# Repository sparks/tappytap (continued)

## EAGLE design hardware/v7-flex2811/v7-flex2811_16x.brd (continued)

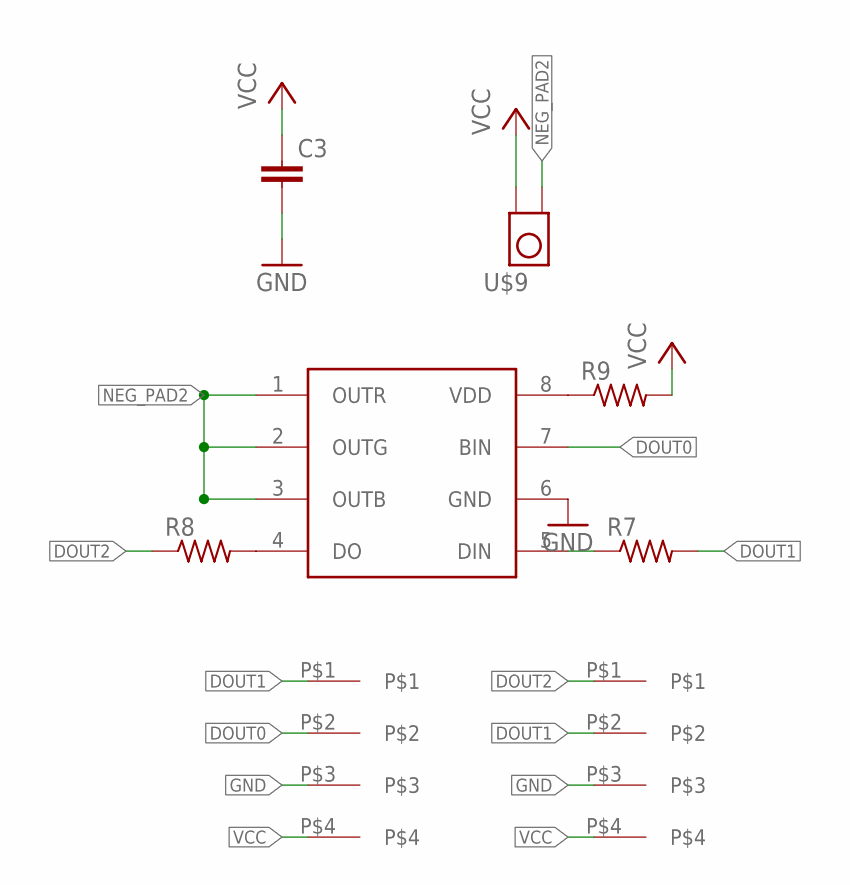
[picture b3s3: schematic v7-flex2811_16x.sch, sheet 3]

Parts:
C3: C-EUC0201; C0201
R7, R8, R9: R-US_R0201; R0201
U$9: TP_4MM_MED_PAD
U$10: WS2818; SO08
U$11, U$12: 4PAD

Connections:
DOUT0: U$10.7 (BIN), U$11.P$2; also elsewhere on the board
DOUT1: R7.2, U$11.P$1, U$12.P$2; also elsewhere on the board
DOUT2: R8.1, U$12.P$1; also elsewhere on the board
GND: C3.2, U$10.6 (GND), U$11.P$3, U$12.P$3; also elsewhere on the board
unnamed: R7.1, U$10.5 (DIN)
unnamed: R8.2, U$10.4 (DO)
unnamed: R9.1, U$10.8 (VDD)
NEG_PAD2: U$9.P$1 (0), U$10.1 (OUTR), U$10.2 (OUTG), U$10.3 (OUTB)
VCC: C3.1, R9.2, U$9.P$2 (1), U$11.P$4, U$12.P$4; also elsewhere on the board

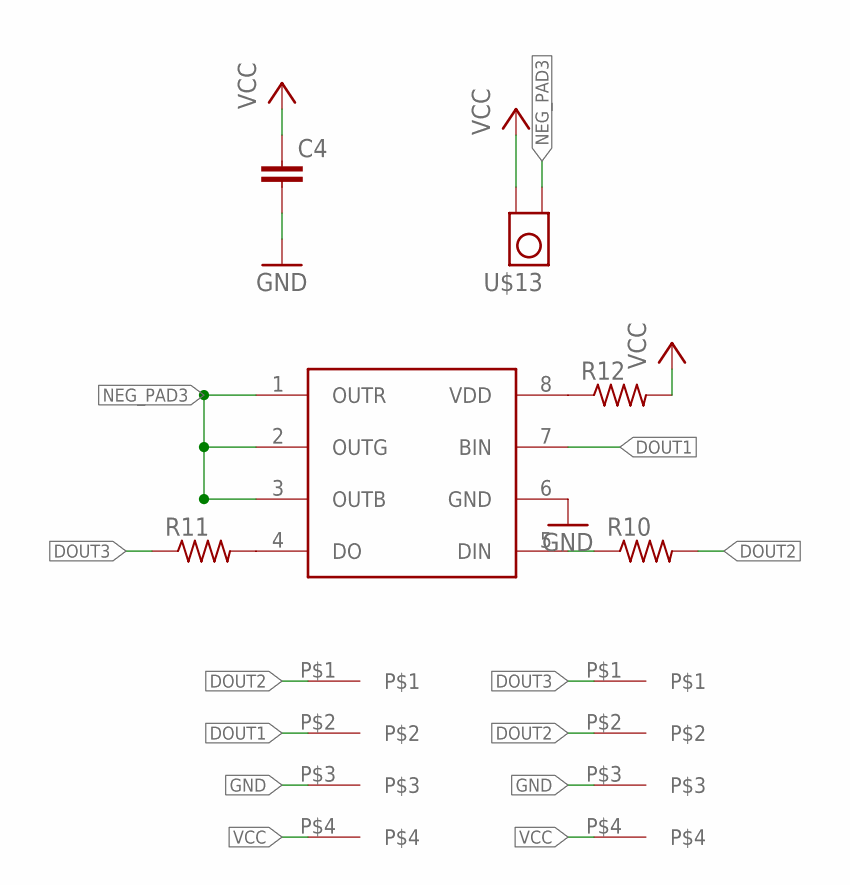
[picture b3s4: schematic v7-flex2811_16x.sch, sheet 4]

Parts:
C4: C-EUC0201; C0201
R10, R11, R12: R-US_R0201; R0201
U$13: TP_4MM_MED_PAD
U$14: WS2818; SO08
U$15, U$16: 4PAD

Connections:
DOUT1: U$14.7 (BIN), U$15.P$2; also elsewhere on the board
DOUT2: R10.2, U$15.P$1, U$16.P$2; also elsewhere on the board
DOUT3: R11.1, U$16.P$1; also elsewhere on the board
GND: C4.2, U$14.6 (GND), U$15.P$3, U$16.P$3; also elsewhere on the board
unnamed: R10.1, U$14.5 (DIN)
unnamed: R11.2, U$14.4 (DO)
unnamed: R12.1, U$14.8 (VDD)
NEG_PAD3: U$13.P$1 (0), U$14.1 (OUTR), U$14.2 (OUTG), U$14.3 (OUTB)
VCC: C4.1, R12.2, U$13.P$2 (1), U$15.P$4, U$16.P$4; also elsewhere on the board

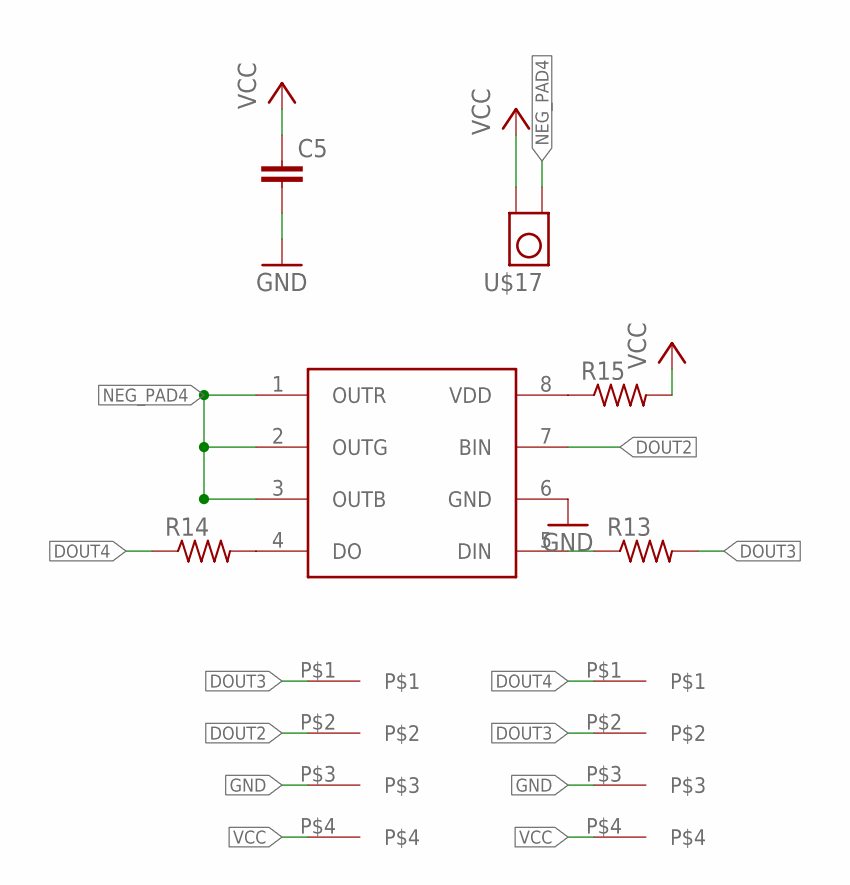
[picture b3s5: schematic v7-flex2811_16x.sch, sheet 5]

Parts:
C5: C-EUC0201; C0201
R13, R14, R15: R-US_R0201; R0201
U$17: TP_4MM_MED_PAD
U$18: WS2818; SO08
U$19, U$20: 4PAD

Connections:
DOUT2: U$18.7 (BIN), U$19.P$2; also elsewhere on the board
DOUT3: R13.2, U$19.P$1, U$20.P$2; also elsewhere on the board
DOUT4: R14.1, U$20.P$1; also elsewhere on the board
GND: C5.2, U$18.6 (GND), U$19.P$3, U$20.P$3; also elsewhere on the board
unnamed: R13.1, U$18.5 (DIN)
unnamed: R14.2, U$18.4 (DO)
unnamed: R15.1, U$18.8 (VDD)
NEG_PAD4: U$17.P$1 (0), U$18.1 (OUTR), U$18.2 (OUTG), U$18.3 (OUTB)
VCC: C5.1, R15.2, U$17.P$2 (1), U$19.P$4, U$20.P$4; also elsewhere on the board

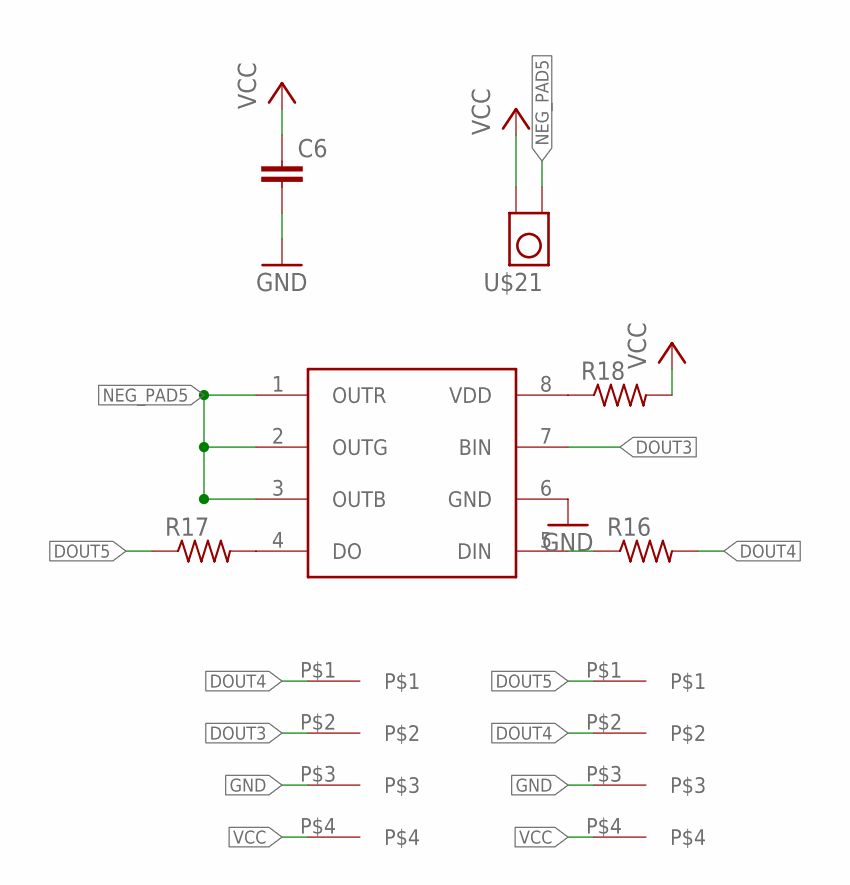
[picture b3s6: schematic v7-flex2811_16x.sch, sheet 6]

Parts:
C6: C-EUC0201; C0201
R16, R17, R18: R-US_R0201; R0201
U$21: TP_4MM_MED_PAD
U$22: WS2818; SO08
U$23, U$24: 4PAD

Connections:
DOUT3: U$22.7 (BIN), U$23.P$2; also elsewhere on the board
DOUT4: R16.2, U$23.P$1, U$24.P$2; also elsewhere on the board
DOUT5: R17.1, U$24.P$1; also elsewhere on the board
GND: C6.2, U$22.6 (GND), U$23.P$3, U$24.P$3; also elsewhere on the board
unnamed: R16.1, U$22.5 (DIN)
unnamed: R17.2, U$22.4 (DO)
unnamed: R18.1, U$22.8 (VDD)
NEG_PAD5: U$21.P$1 (0), U$22.1 (OUTR), U$22.2 (OUTG), U$22.3 (OUTB)
VCC: C6.1, R18.2, U$21.P$2 (1), U$23.P$4, U$24.P$4; also elsewhere on the board

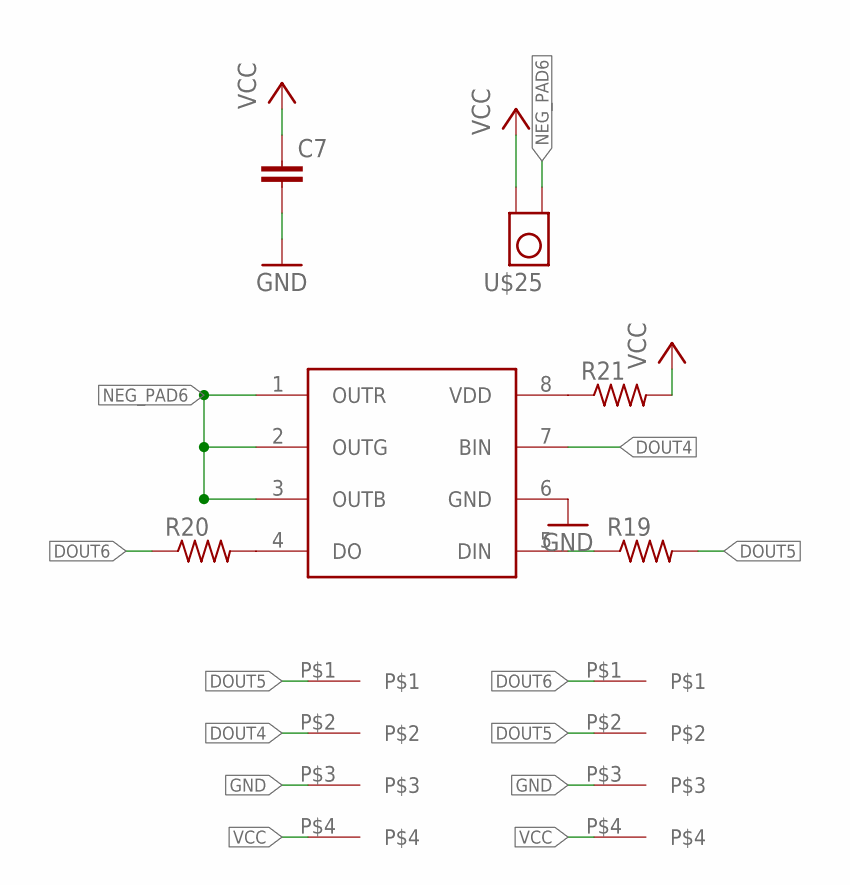
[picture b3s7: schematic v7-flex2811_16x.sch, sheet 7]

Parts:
C7: C-EUC0201; C0201
R19, R20, R21: R-US_R0201; R0201
U$25: TP_4MM_MED_PAD
U$26: WS2818; SO08
U$27, U$28: 4PAD

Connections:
DOUT4: U$26.7 (BIN), U$27.P$2; also elsewhere on the board
DOUT5: R19.2, U$27.P$1, U$28.P$2; also elsewhere on the board
DOUT6: R20.1, U$28.P$1; also elsewhere on the board
GND: C7.2, U$26.6 (GND), U$27.P$3, U$28.P$3; also elsewhere on the board
unnamed: R19.1, U$26.5 (DIN)
unnamed: R20.2, U$26.4 (DO)
unnamed: R21.1, U$26.8 (VDD)
NEG_PAD6: U$25.P$1 (0), U$26.1 (OUTR), U$26.2 (OUTG), U$26.3 (OUTB)
VCC: C7.1, R21.2, U$25.P$2 (1), U$27.P$4, U$28.P$4; also elsewhere on the board

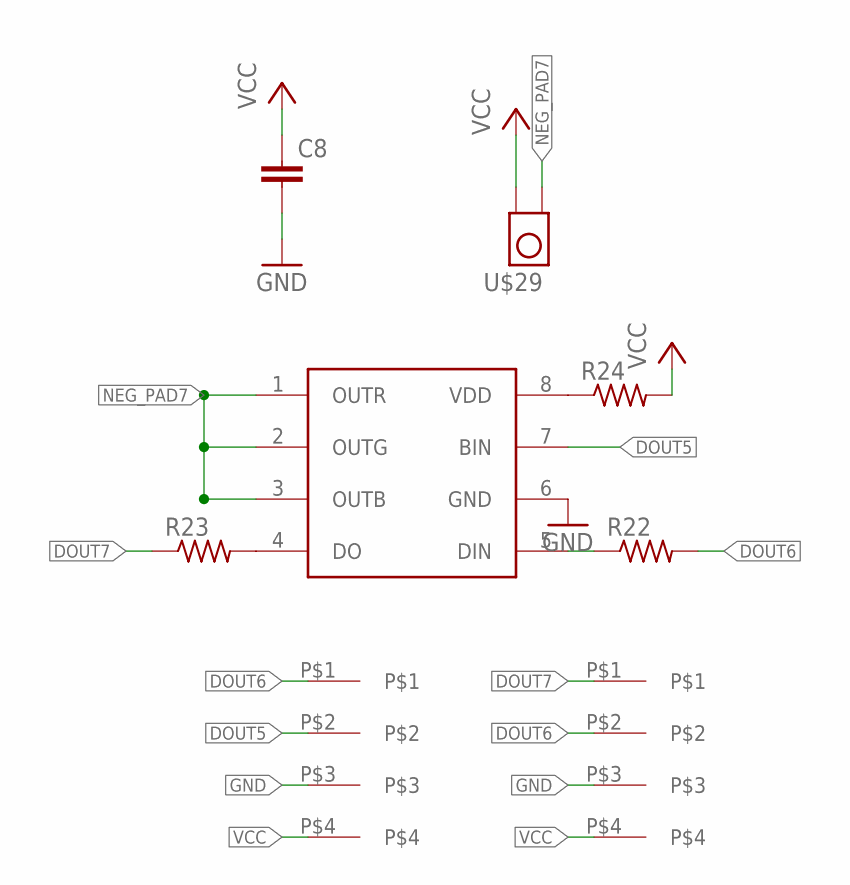
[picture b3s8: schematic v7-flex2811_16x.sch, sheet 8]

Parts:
C8: C-EUC0201; C0201
R22, R23, R24: R-US_R0201; R0201
U$29: TP_4MM_MED_PAD
U$30: WS2818; SO08
U$31, U$32: 4PAD

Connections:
DOUT5: U$30.7 (BIN), U$31.P$2; also elsewhere on the board
DOUT6: R22.2, U$31.P$1, U$32.P$2; also elsewhere on the board
DOUT7: R23.1, U$32.P$1; also elsewhere on the board
GND: C8.2, U$30.6 (GND), U$31.P$3, U$32.P$3; also elsewhere on the board
unnamed: R22.1, U$30.5 (DIN)
unnamed: R23.2, U$30.4 (DO)
unnamed: R24.1, U$30.8 (VDD)
NEG_PAD7: U$29.P$1 (0), U$30.1 (OUTR), U$30.2 (OUTG), U$30.3 (OUTB)
VCC: C8.1, R24.2, U$29.P$2 (1), U$31.P$4, U$32.P$4; also elsewhere on the board

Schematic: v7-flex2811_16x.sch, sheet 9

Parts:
C9: C-EUC0201; C0201
R25, R26, R27: R-US_R0201; R0201
U$33: TP_4MM_MED_PAD
U$34: WS2818; SO08
U$35, U$36: 4PAD

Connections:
DOUT6: U$34.7 (BIN), U$35.P$2; also elsewhere on the board
DOUT7: R25.2, U$35.P$1, U$36.P$2; also elsewhere on the board
DOUT8: R26.1, U$36.P$1; also elsewhere on the board
GND: C9.2, U$34.6 (GND), U$35.P$3, U$36.P$3; also elsewhere on the board
unnamed: R25.1, U$34.5 (DIN)
unnamed: R26.2, U$34.4 (DO)
unnamed: R27.1, U$34.8 (VDD)
NEG_PAD8: U$33.P$1 (0), U$34.1 (OUTR), U$34.2 (OUTG), U$34.3 (OUTB)
VCC: C9.1, R27.2, U$33.P$2 (1), U$35.P$4, U$36.P$4; also elsewhere on the board

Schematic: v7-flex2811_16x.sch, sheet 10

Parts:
C10: C-EUC0201; C0201
R28, R29, R30: R-US_R0201; R0201
U$37: TP_4MM_MED_PAD
U$38: WS2818; SO08
U$39, U$40: 4PAD

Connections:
DOUT7: U$38.7 (BIN), U$39.P$2; also elsewhere on the board
DOUT8: R28.2, U$39.P$1, U$40.P$2; also elsewhere on the board
DOUT9: R29.1, U$40.P$1; also elsewhere on the board
GND: C10.2, U$38.6 (GND), U$39.P$3, U$40.P$3; also elsewhere on the board
unnamed: R28.1, U$38.5 (DIN)
unnamed: R29.2, U$38.4 (DO)
unnamed: R30.1, U$38.8 (VDD)
NEG_PAD9: U$37.P$1 (0), U$38.1 (OUTR), U$38.2 (OUTG), U$38.3 (OUTB)
VCC: C10.1, R30.2, U$37.P$2 (1), U$39.P$4, U$40.P$4; also elsewhere on the board

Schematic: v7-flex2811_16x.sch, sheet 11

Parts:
C11: C-EUC0201; C0201
R31, R32, R33: R-US_R0201; R0201
U$41: TP_4MM_MED_PAD
U$42: WS2818; SO08
U$43, U$44: 4PAD

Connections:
DOUT8: U$42.7 (BIN), U$43.P$2; also elsewhere on the board
DOUT9: R31.2, U$43.P$1, U$44.P$2; also elsewhere on the board
DOUT10: R32.1, U$44.P$1; also elsewhere on the board
GND: C11.2, U$42.6 (GND), U$43.P$3, U$44.P$3; also elsewhere on the board
unnamed: R31.1, U$42.5 (DIN)
unnamed: R32.2, U$42.4 (DO)
unnamed: R33.1, U$42.8 (VDD)
NEG_PAD10: U$41.P$1 (0), U$42.1 (OUTR), U$42.2 (OUTG), U$42.3 (OUTB)
VCC: C11.1, R33.2, U$41.P$2 (1), U$43.P$4, U$44.P$4; also elsewhere on the board

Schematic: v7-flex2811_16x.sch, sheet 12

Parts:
C12: C-EUC0201; C0201
R34, R35, R36: R-US_R0201; R0201
U$45: TP_4MM_MED_PAD
U$46: WS2818; SO08
U$47, U$48: 4PAD

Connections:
DOUT9: U$46.7 (BIN), U$47.P$2; also elsewhere on the board
DOUT10: R34.2, U$47.P$1, U$48.P$2; also elsewhere on the board
DOUT11: R35.1, U$48.P$1; also elsewhere on the board
GND: C12.2, U$46.6 (GND), U$47.P$3, U$48.P$3; also elsewhere on the board
unnamed: R34.1, U$46.5 (DIN)
unnamed: R35.2, U$46.4 (DO)
unnamed: R36.1, U$46.8 (VDD)
NEG_PAD11: U$45.P$1 (0), U$46.1 (OUTR), U$46.2 (OUTG), U$46.3 (OUTB)
VCC: C12.1, R36.2, U$45.P$2 (1), U$47.P$4, U$48.P$4; also elsewhere on the board

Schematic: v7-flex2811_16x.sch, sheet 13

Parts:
C13: C-EUC0201; C0201
R37, R38, R39: R-US_R0201; R0201
U$49: TP_4MM_MED_PAD
U$50: WS2818; SO08
U$51, U$52: 4PAD

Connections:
DOUT10: U$50.7 (BIN), U$51.P$2; also elsewhere on the board
DOUT11: R37.2, U$51.P$1, U$52.P$2; also elsewhere on the board
DOUT12: R38.1, U$52.P$1; also elsewhere on the board
GND: C13.2, U$50.6 (GND), U$51.P$3, U$52.P$3; also elsewhere on the board
unnamed: R37.1, U$50.5 (DIN)
unnamed: R38.2, U$50.4 (DO)
unnamed: R39.1, U$50.8 (VDD)
NEG_PAD12: U$49.P$1 (0), U$50.1 (OUTR), U$50.2 (OUTG), U$50.3 (OUTB)
VCC: C13.1, R39.2, U$49.P$2 (1), U$51.P$4, U$52.P$4; also elsewhere on the board

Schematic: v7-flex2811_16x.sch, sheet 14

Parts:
C14: C-EUC0201; C0201
R40, R41, R42: R-US_R0201; R0201
U$53: TP_4MM_MED_PAD
U$54: WS2818; SO08
U$55, U$56: 4PAD

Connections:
DOUT11: U$54.7 (BIN), U$55.P$2; also elsewhere on the board
DOUT12: R40.2, U$55.P$1, U$56.P$2; also elsewhere on the board
DOUT13: R41.1, U$56.P$1; also elsewhere on the board
GND: C14.2, U$54.6 (GND), U$55.P$3, U$56.P$3; also elsewhere on the board
unnamed: R40.1, U$54.5 (DIN)
unnamed: R41.2, U$54.4 (DO)
unnamed: R42.1, U$54.8 (VDD)
NEG_PAD13: U$53.P$1 (0), U$54.1 (OUTR), U$54.2 (OUTG), U$54.3 (OUTB)
VCC: C14.1, R42.2, U$53.P$2 (1), U$55.P$4, U$56.P$4; also elsewhere on the board

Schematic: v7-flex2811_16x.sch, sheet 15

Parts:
C15: C-EUC0201; C0201
R43, R44, R45: R-US_R0201; R0201
U$57: TP_4MM_MED_PAD
U$58: WS2818; SO08
U$59, U$60: 4PAD

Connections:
DOUT12: U$58.7 (BIN), U$59.P$2; also elsewhere on the board
DOUT13: R43.2, U$59.P$1, U$60.P$2; also elsewhere on the board
DOUT14: R44.1, U$60.P$1; also elsewhere on the board
GND: C15.2, U$58.6 (GND), U$59.P$3, U$60.P$3; also elsewhere on the board
unnamed: R43.1, U$58.5 (DIN)
unnamed: R44.2, U$58.4 (DO)
unnamed: R45.1, U$58.8 (VDD)
NEG_PAD14: U$57.P$1 (0), U$58.1 (OUTR), U$58.2 (OUTG), U$58.3 (OUTB)
VCC: C15.1, R45.2, U$57.P$2 (1), U$59.P$4, U$60.P$4; also elsewhere on the board

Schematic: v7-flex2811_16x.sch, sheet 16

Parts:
C16: C-EUC0201; C0201
R46, R47, R48: R-US_R0201; R0201
U$61: TP_4MM_MED_PAD
U$62: WS2818; SO08
U$63, U$64: 4PAD

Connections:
DOUT13: U$62.7 (BIN), U$63.P$2; also elsewhere on the board
DOUT14: R46.2, U$63.P$1, U$64.P$2; also elsewhere on the board
DOUT15: R47.1, U$64.P$1
GND: C16.2, U$62.6 (GND), U$63.P$3, U$64.P$3; also elsewhere on the board
unnamed: R46.1, U$62.5 (DIN)
unnamed: R47.2, U$62.4 (DO)
unnamed: R48.1, U$62.8 (VDD)
NEG_PAD15: U$61.P$1 (0), U$62.1 (OUTR), U$62.2 (OUTG), U$62.3 (OUTB)
VCC: C16.1, R48.2, U$61.P$2 (1), U$63.P$4, U$64.P$4; also elsewhere on the board

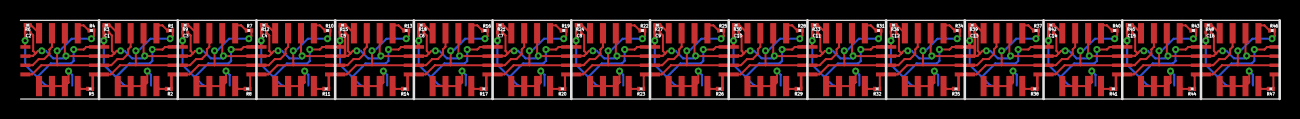
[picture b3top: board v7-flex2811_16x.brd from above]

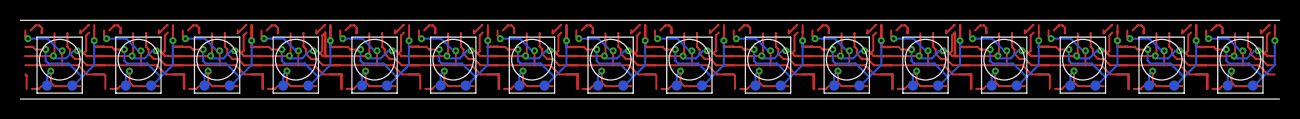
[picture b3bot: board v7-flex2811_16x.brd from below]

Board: 2 copper layers, 124.0 x 7.8 mm, 128 parts (16 on the bottom side), 84 nets.

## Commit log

2017-06-22 Initial import
2017-06-22 More comments
2017-06-22 A TODO
2017-06-22 README
2017-06-23 Add a wiring diagram
2017-07-19 Add pio version of firmware
2017-07-19 Remove dead file
2017-07-19 Read me
2018-01-23 First pass (unfinshed routing) on new PCB iteration
2018-01-23 Finished routing on first pass
2018-01-24 Finalize routing
2018-01-29 Final with gerbers for v2
2018-01-29 Small spacing tweaks
2018-01-31 Fix spacing issue for pcbway
2018-02-14 Add env to pio for uno
2018-02-22 Some firmware updates
2018-02-27 Fix a counter error
2018-02-28 Add atmega master
2018-04-05 Add a control software in processing
2018-04-06 Adjust for correct bit format
2018-04-06 Firmware to go with processing sketch (not quite done)
2018-04-12 Finish driver code
2018-04-12 Defaults for the cpp wave values
2018-04-12 Fix some small bugs and add debug serial to cpp
2018-04-12 Auto select serial port in processing
2018-04-12 Debug incomming serial in arduino
2018-04-12 Don't debug that serial anymore (1 board in cpp for simple debug)
2018-04-12 Some tweaks as I test, change the conf range
2018-04-12 Fix value init bug
2018-04-15 Make a cool drag thingy for the wave
2018-04-15 Adjust range to 10uS and finish the new interface
2018-04-20 Fix some small bugs
2018-04-20 Side by side controls
2018-04-22 print statement removed
2018-04-26 Error in period calculation
2018-04-26 Math issue
2018-04-26 Tweaks as I test
2018-05-02 Fix shift issue and some tweaks
2018-05-03 Add files for a v3
2018-05-04 Tappytap v3 design done with gerbers
2018-05-04 Cleanup main there was a bug in committed code
2018-05-04 Make the connection be dir reversing + period adjust
2018-05-15 Small tweak to debug print outs
2018-06-17 Fix another timing bug
2018-06-17 Send a ready string to tell processing we're g2g
2018-06-17 Tweaks
    * Make shift lock taps in until next mouse / shift
    * Make on the fly conf work
    * Conf on startup (with the "ready" string from arduino)
    * Change the default conf system to match the onscreen printout
2018-06-17 lock mode for testing
2018-06-18 gitignore
2018-07-04 Square boards with / without through hole
2018-07-05 Ship v4-sur
2018-12-02 Import the tappytap flex board from tom
2018-12-02 Flex version
2018-12-04 Gerbers
2019-04-06 v6 flex PCBs
2019-04-06 Gerbers and some related tweaks
2019-04-30 very incomplete modifications to processing-bridge code to adapt it to TLE chips
2019-04-30 intermediary changes moving to v6
2019-04-30 Updates for the new traversal order of tappy taps
2019-04-30 Revert old code for posterity
2019-05-01 working SPI array traversal
2019-05-01 Small cleanup
2019-05-01 Fix the loading issues between processing and arduino
2019-05-01 Playing with variable naming
2019-05-01 Some whitespace
2019-05-01 Some comments for how to use
2019-05-01 Working briefly on the traversal
2019-05-01 Working on a readme
2019-05-01 Remove the prints
2019-05-01 Cleanup print
2019-05-01 Add some docs
2019-05-01 Revert to working
2019-05-01 Debug > 8 ICs
2019-05-01 More random debugging
2019-05-01 More fiddling
2019-05-01 Debug working hack
2019-05-01 Making my hack work
2019-05-01 Revert the hack it doesn't actually work
2019-05-12 firmware workaround with separate cs lines
2019-05-13 remapping commands from processing interface to match with new SPI configuration
2019-05-13 made pin assignment/init more flexible for CS lines
2019-06-05 Add pattern playback function
    Adds a pattern playback function to play patterns and a slider to adjust the playback rate. Also makes sure click+drag on sliders always stays on the same slider instead of switching between differen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
2019-06-06 Enable serial connection by default
2019-07-15 Make ints bigger
2019-10-21 Some preliminary schematic and layout
    Pausing to ask some questions about sizing
    and package usage
2019-10-25 first draft tapper strip
2019-10-26 Rework the single for more clearance to make fab easier
    Was concerned about how tight the passives were for
    assmebly, have just spread it out a bit
    Also made the WS2818 pads slightly smaller so we have more clearance
2019-10-28 Rebuild a 32 strip from the slightly update single
    Single has more room to place passives and slightly smaller
    2818 pads so that there's more clearance with the edge
2019-10-29 More edit for manufacturability
    Add a preliminary BOM
    Add labels for the ICs for assembly
2019-10-29 Generating gerbers for the build
2019-10-31 More exporting and organizing
2019-10-31 Update gitignore
2019-11-16 Add a better pin one mark
2019-11-30 Add the eagle file for tappy v7 connectors
2020-01-26 Import Tom's files and make some minor silk screen adjustement
    * Move registration on DFN 8
    * resize the part names
2020-01-26 Exported gerbers rev 1
2020-01-26 Remove unneeded file
2020-01-26 Fix error with minium drill sizes and reexport rev1
2020-01-29 Corrected the BOM there was some export issue
2020-04-01 Add a BOM from pcbway
2020-07-30 Quick Breakout for the PAM Hbridge
